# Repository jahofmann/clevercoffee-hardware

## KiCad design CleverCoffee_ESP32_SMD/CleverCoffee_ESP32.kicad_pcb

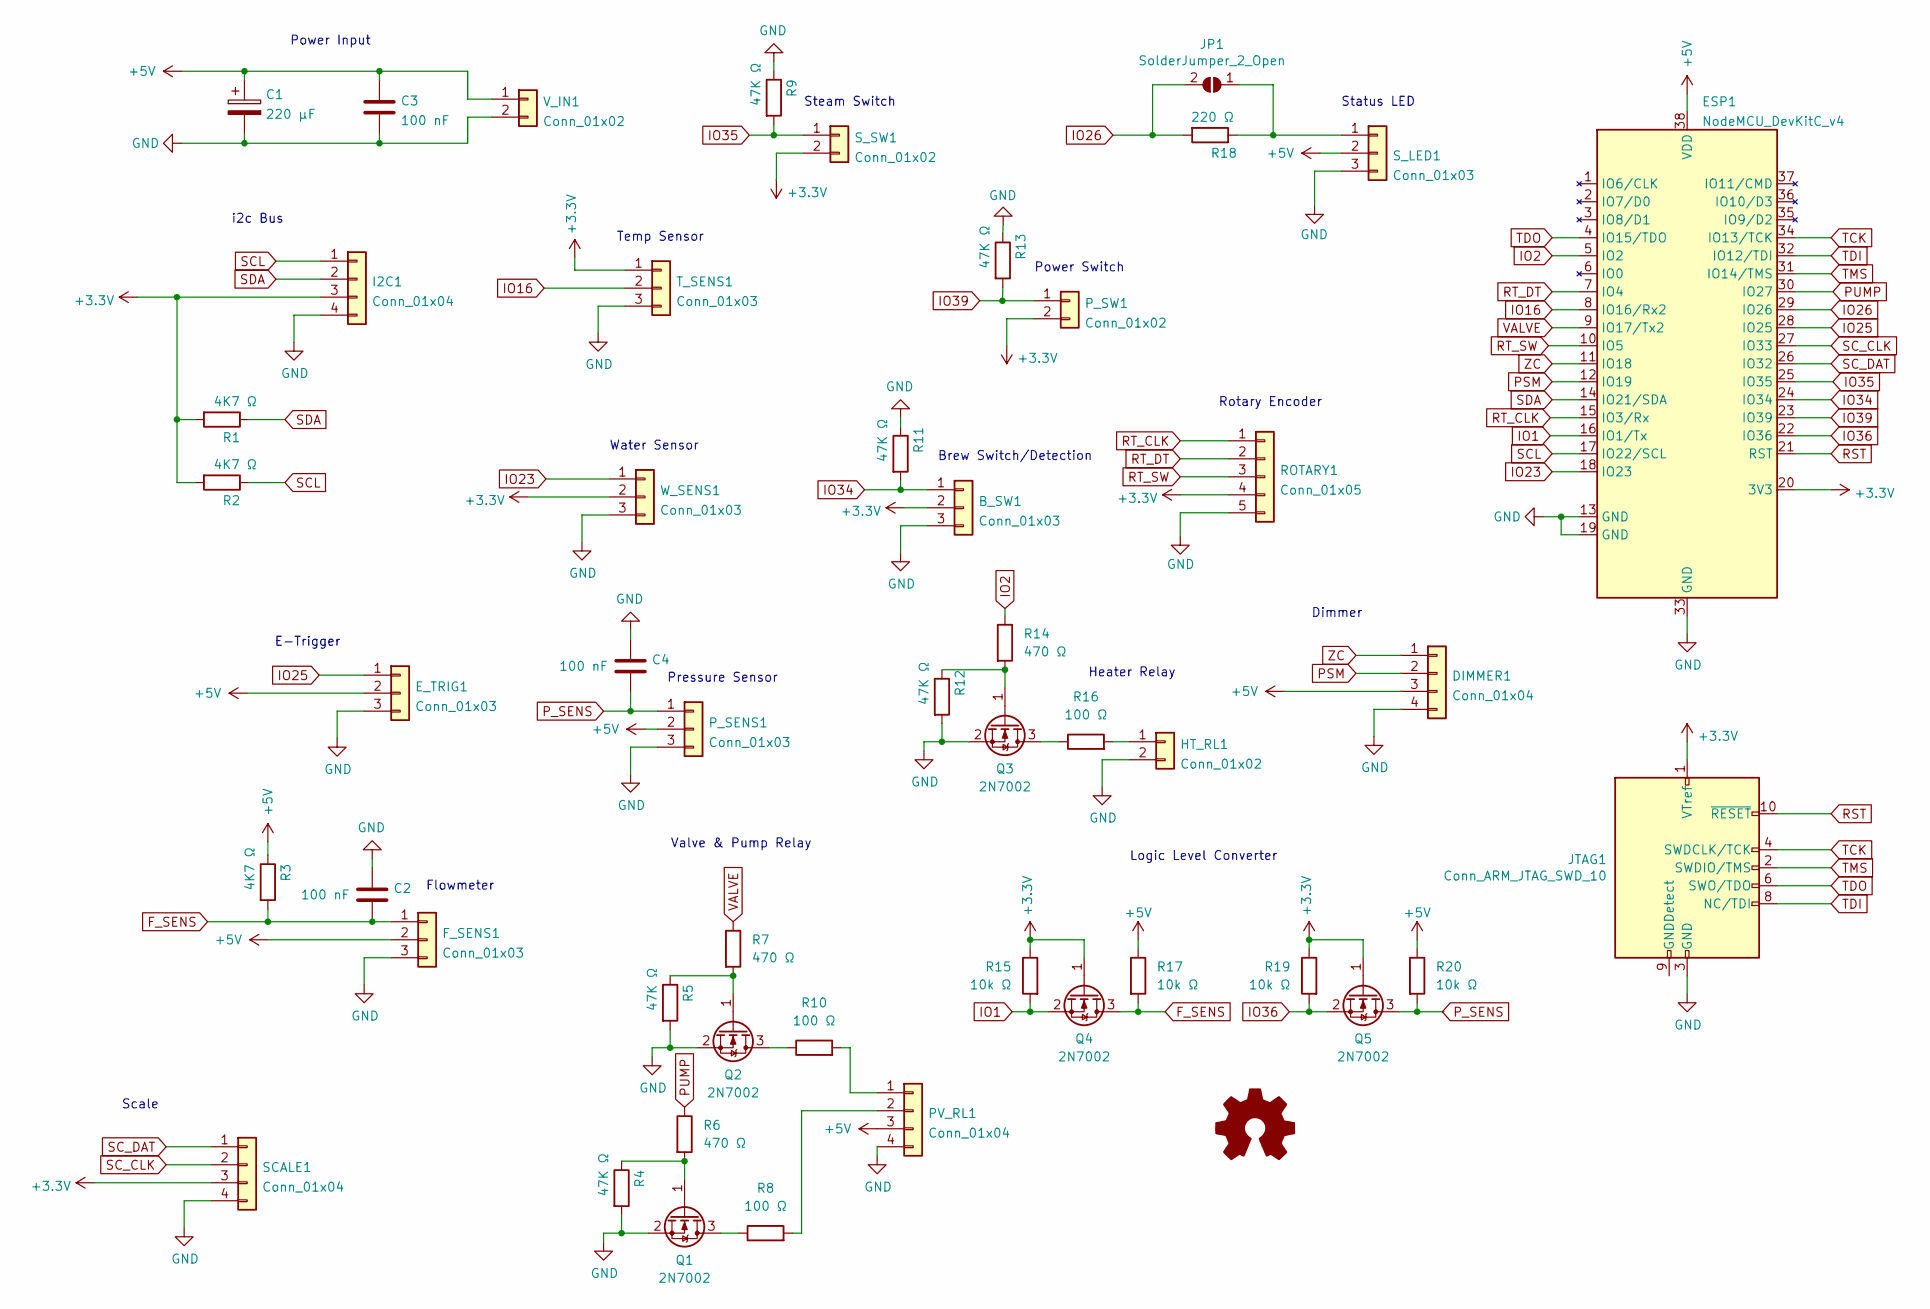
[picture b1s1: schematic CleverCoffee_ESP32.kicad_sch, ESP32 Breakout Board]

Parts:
B_SW1: Conn_01x03; PinSocket_1x03_P2.54mm_Vertical; JLCPCB BOM false
C1: 220 μF; CP_Radial_D8.0mm_P3.80mm; JLCPCB BOM false
C2, C3, C4: 100 nF; C_0603_1608Metric; LCSC Part C14663
DIMMER1: Conn_01x04; PinSocket_1x04_P2.54mm_Vertical; JLCPCB BOM false
ESP1: NodeMCU_DevKitC_v4; NodeMCU DevKitC v4; JLCPCB BOM false
E_TRIG1: Conn_01x03; PinSocket_1x03_P2.54mm_Vertical; JLCPCB BOM false
F_SENS1: Conn_01x03; PinSocket_1x03_P2.54mm_Vertical; JLCPCB BOM false
HT_RL1: Conn_01x02; PinSocket_1x02_P2.54mm_Vertical; JLCPCB BOM false
I2C1: Conn_01x04; PinSocket_1x04_P2.54mm_Vertical; JLCPCB BOM false
JP1: SolderJumper_2_Open; SolderJumper-2_P1.3mm_Open_Pad1.0x1.5mm; JLCPCB BOM false
JTAG1: Conn_ARM_JTAG_SWD_10; PinHeader_2x05_P2.54mm_Vertical; JLCPCB BOM false
PV_RL1: Conn_01x04; PinSocket_1x04_P2.54mm_Vertical; JLCPCB BOM false
P_SENS1: Conn_01x03; PinSocket_1x03_P2.54mm_Vertical; JLCPCB BOM false
P_SW1: Conn_01x02; PinSocket_1x02_P2.54mm_Vertical; JLCPCB BOM false
Q1, Q2, Q3, Q4, Q5: 2N7002; SOT-23; LCSC Part C8545
R1, R2, R3: 4K7 Ω; C_0603_1608Metric; LCSC Part C23162
R4, R5, R9, R11, R12, R13: 47K Ω; C_0603_1608Metric; LCSC Part C25819
R6, R7, R14: 470 Ω; C_0603_1608Metric; LCSC Part C23179
R8, R10, R16: 100 Ω; C_0603_1608Metric; LCSC Part C22775
R15, R17, R19, R20: 10k Ω; R_0603_1608Metric; LCSC Part C25804
R18: 220 Ω; C_0603_1608Metric; LCSC Part C22962
ROTARY1: Conn_01x05; PinSocket_1x05_P2.54mm_Vertical; JLCPCB BOM false
SCALE1: Conn_01x04; PinSocket_1x04_P2.54mm_Vertical; JLCPCB BOM false
S_LED1: Conn_01x03; PinSocket_1x03_P2.54mm_Vertical; JLCPCB BOM false
S_SW1: Conn_01x02; PinSocket_1x02_P2.54mm_Vertical; JLCPCB BOM false
T_SENS1: Conn_01x03; PinSocket_1x03_P2.54mm_Vertical; JLCPCB BOM false
V_IN1: Conn_01x02; PinSocket_1x02_P2.54mm_Vertical; JLCPCB BOM false
W_SENS1: Conn_01x03; PinSocket_1x03_P2.54mm_Vertical; JLCPCB BOM false

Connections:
+3V3: B_SW1.2, ESP1.20 (3V3), I2C1.3, JTAG1.1 (VTref), P_SW1.2, Q4.1 (G), Q5.1 (G), R1.2, R2.2, R15.1, R19.1, ROTARY1.4, SCALE1.3, S_SW1.2, T_SENS1.1, W_SENS1.2
+5V: C1.1, C3.1, DIMMER1.3, ESP1.38 (VDD), E_TRIG1.2, F_SENS1.2, PV_RL1.3, P_SENS1.2, R3.1, R17.1, R20.1, S_LED1.2, V_IN1.1
F_SENS: C2.2, F_SENS1.1, Q4.3 (D), R3.2, R17.2
GND: B_SW1.3, C1.2, C2.1, C3.2, C4.1, DIMMER1.4, ESP1.13 (GND), ESP1.19 (GND), ESP1.33 (GND), E_TRIG1.3, F_SENS1.3, HT_RL1.2, I2C1.4, JTAG1.3 (GND), JTAG1.5 (GND), PV_RL1.4, P_SENS1.3, Q1.2 (S), Q2.2 (S), Q3.2 (S), R4.2, R5.2, R9.1, R11.1, R12.2, R13.1, ROTARY1.5, SCALE1.4, S_LED1.3, T_SENS1.3, V_IN1.2, W_SENS1.3
IO1: ESP1.16 (IO1/Tx), Q4.2 (S), R15.2
IO2: ESP1.5 (IO2), R14.1
IO16: ESP1.8 (IO16/Rx2), T_SENS1.2
IO23: ESP1.18 (IO23), W_SENS1.1
IO25: ESP1.28 (IO25), E_TRIG1.1
IO26: ESP1.29 (IO26), JP1.2 (B), R18.2
IO34: B_SW1.1, ESP1.24 (IO34), R11.2
IO35: ESP1.25 (IO35), R9.2, S_SW1.1
IO36: ESP1.22 (IO36), Q5.2 (S), R19.2
IO39: ESP1.23 (IO39), P_SW1.1, R13.2
unnamed: HT_RL1.1, R16.2
unnamed: JP1.1 (A), R18.1, S_LED1.1
unnamed: PV_RL1.1, R10.2
unnamed: PV_RL1.2, R8.2
unnamed: Q1.3 (D), R8.1
unnamed: Q1.1 (G), R4.1, R6.2
unnamed: Q2.3 (D), R10.1
unnamed: Q2.1 (G), R5.1, R7.2
unnamed: Q3.3 (D), R16.1
unnamed: Q3.1 (G), R12.1, R14.2
PSM: DIMMER1.2, ESP1.12 (IO19)
PUMP: ESP1.30 (IO27), R6.1
P_SENS: C4.2, P_SENS1.1, Q5.3 (D), R20.2
RST: ESP1.21 (RST), JTAG1.10 (~RESET)
RT_CLK: ESP1.15 (IO3/Rx), ROTARY1.1
RT_DT: ESP1.7 (IO4), ROTARY1.2
RT_SW: ESP1.10 (IO5), ROTARY1.3
SCL: ESP1.17 (IO22/SCL), I2C1.1, R2.1
SC_CLK: ESP1.27 (IO33), SCALE1.2
SC_DAT: ESP1.26 (IO32), SCALE1.1
SDA: ESP1.14 (IO21/SDA), I2C1.2, R1.1
TCK: ESP1.34 (IO13/TCK), JTAG1.4 (SWDCLK/TCK)
TDI: ESP1.32 (IO12/TDI), JTAG1.8 (NC/TDI)
TDO: ESP1.4 (IO15/TDO), JTAG1.6 (SWO/TDO)
TMS: ESP1.31 (IO14/TMS), JTAG1.2 (SWDIO/TMS)
VALVE: ESP1.9 (IO17/Tx2), R7.1
ZC: DIMMER1.1, ESP1.11 (IO18)

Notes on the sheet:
Status LED
i2c Bus
Logic Level Converter
Power Switch
Brew Switch/Detection
E-Trigger
Temp Sensor
Rotary Encoder
Steam Switch
Heater Relay
Scale
Pressure Sensor
Dimmer
Flowmeter
Power Input
Valve & Pump Relay
Water Sensor

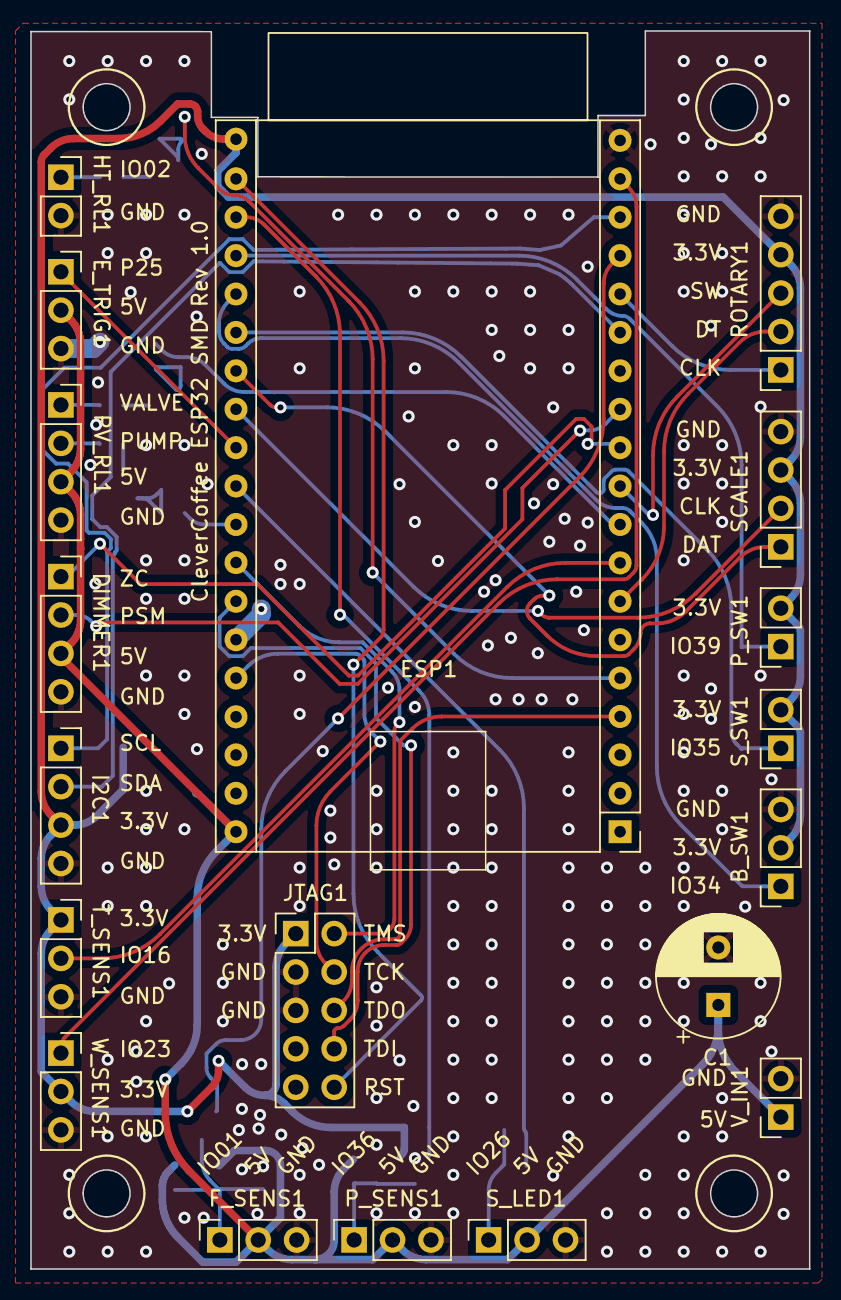
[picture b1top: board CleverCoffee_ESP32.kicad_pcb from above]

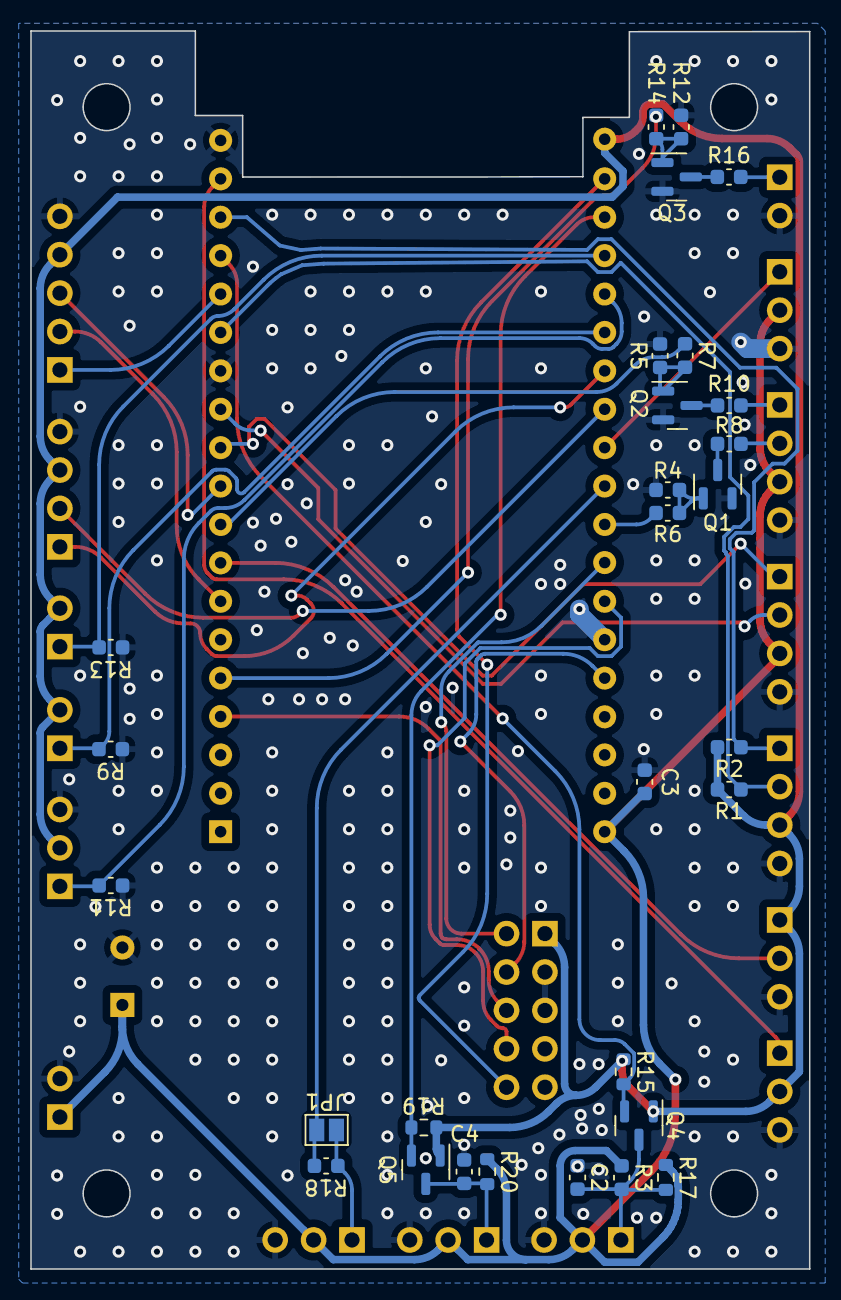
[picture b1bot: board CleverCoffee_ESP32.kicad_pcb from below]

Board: 2 copper layers, 51.5 x 81.9 mm, 48 parts (29 on the bottom side), 41 nets.

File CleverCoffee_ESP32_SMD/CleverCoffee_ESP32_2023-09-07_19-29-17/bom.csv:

Designator,Footprint,Quantity,Value,LCSC Part #
"B_SW1, E_TRIG1, F_SENS1, P_SENS1, S_LED1, T_SENS1, W_SENS1",PinSocket_1x03_P2.54mm_Vertical,7,Conn_01x03,
C1,CP_Radial_D8.0mm_P3.80mm,1,220 μF,
"C2, C3, C4",0603,3,100 nF,C14663
"DIMMER1, I2C1, PV_RL1, SCALE1",PinSocket_1x04_P2.54mm_Vertical,4,Conn_01x04,
ESP1,NodeMCU DevKitC v4,1,NodeMCU_DevKitC_v4,
"HT_RL1, P_SW1, S_SW1, V_IN1",PinSocket_1x02_P2.54mm_Vertical,4,Conn_01x02,
JP1,SolderJumper-2_P1.3mm_Open_Pad1.0x1.5mm,1,SolderJumper_2_Open,
JTAG1,PinHeader_2x05_P2.54mm_Vertical,1,Conn_ARM_JTAG_SWD_10,
"Q1, Q2, Q3, Q4, Q5",SOT-23,5,2N7002,C8545
"R1, R2, R3",0603,3,4K7 Ω,C23162
"R10, R16, R8",0603,3,100 Ω,C22775
"R11, R12, R13, R4, R5, R9",0603,6,47K Ω,C25819
"R14, R6, R7",0603,3,470 Ω,C23179
"R15, R17, R19, R20",0603,4,10k Ω,C25804
R18,0603,1,220 Ω,C22962
ROTARY1,PinSocket_1x05_P2.54mm_Vertical,1,Conn_01x05,

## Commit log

2023-09-07 Started reworking PCB for JLCPCB assembly
2023-09-07 Finishes SMD version for production
2023-09-08 Finalize DRC and add production files
2023-09-08 Final touches and production files
2023-10-04 Adds SPICE model
